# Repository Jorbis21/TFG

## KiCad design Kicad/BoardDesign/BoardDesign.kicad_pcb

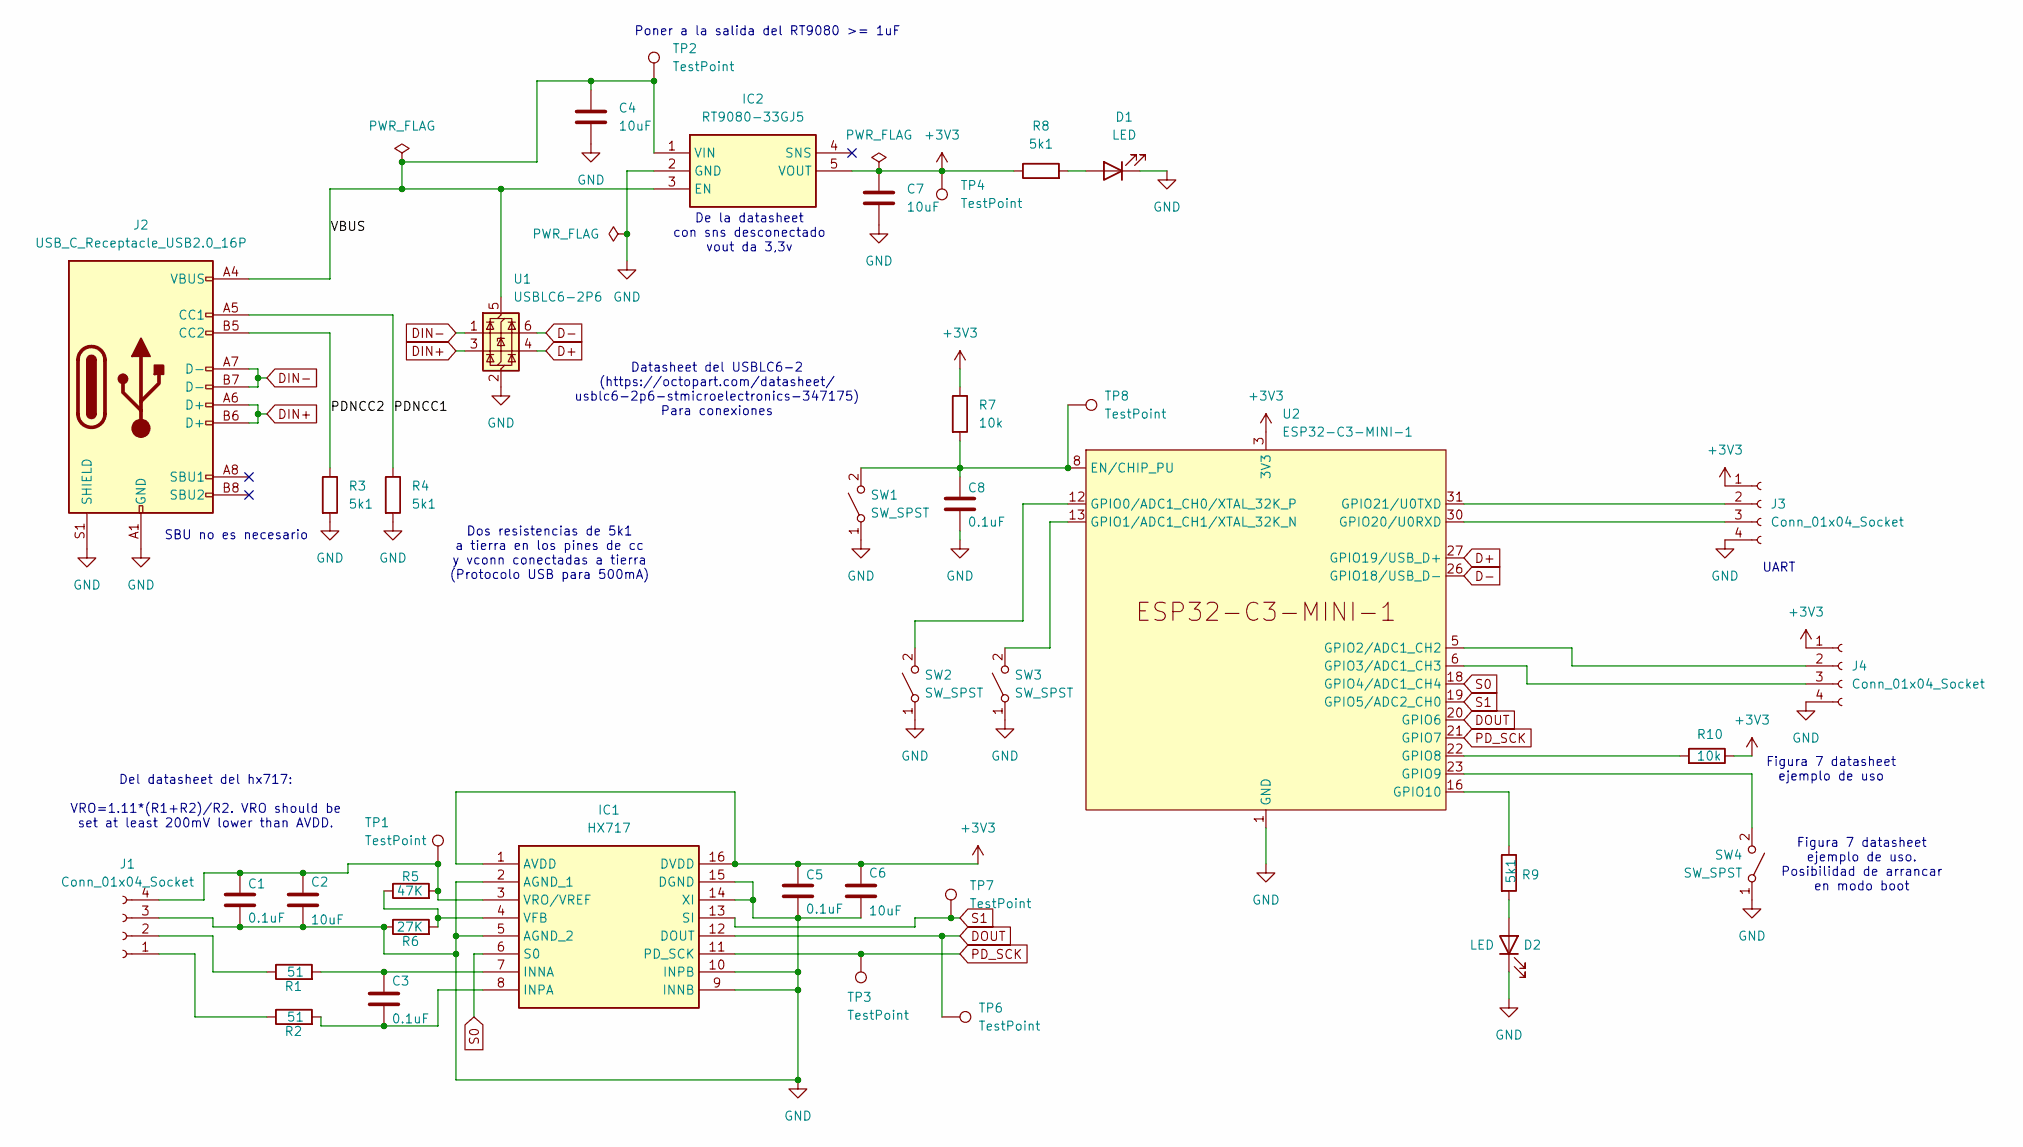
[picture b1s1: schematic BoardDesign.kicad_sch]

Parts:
C1, C3, C5, C8: 0.1uF; C_0603_1608Metric; JLCPCB C14663
C2, C4, C6, C7: 10uF; C_0603_1608Metric; JLCPCB C19702
D1, D2: LED; LED_0603_1608Metric
IC1: HX717; SOP-16_3.9x9.9mm_P1.27mm; Manufacturer_Part_Number HX717; JLCPCB C575394
IC2: RT9080-33GJ5; TSOT-23-5; Manufacturer_Part_Number RT9080-33GJ5; Mouser Part Number 835-RT9080-33GJ5
J1, J3, J4: Conn_01x04_Socket; PinHeader_1x04_P2.54mm_Vertical; JLCPCB C5116483
J2: USB_C_Receptacle_USB2.0_16P; USB_C_Receptacle_GCT_USB4105-xx-A_16P_TopMnt_Horizontal; JLCPCB C5116483
R1, R2: 51; R_0603_1608Metric
R3, R4, R8, R9: 5k1; R_0603_1608Metric
R5: 47K; R_0603_1608Metric
R6: 27K; R_0603_1608Metric
R7, R10: 10k; R_0603_1608Metric
SW1, SW2, SW3, SW4: SW_SPST; TS1187ABAB; JLCPCB C318884
TP1, TP2, TP3, TP4, TP6, TP7, TP8: TestPoint; TestPoint_Pad_D1.5mm_nosilk
U1: USBLC6-2P6; SOT-666; JLCPCB C2827693
U2: ESP32-C3-MINI-1; JLCPCB C2911374

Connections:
+3V3: C5.1, C6.1, C7.1, IC1.1 (AVDD), IC1.16 (DVDD), IC2.5 (VOUT), J3.1, J4.1, R7.1, R8.1, R10.1, TP4.1, U2.3 (3V3)
/PDNCC1: J2.A5 (CC1), R4.1
/PDNCC2: J2.B5 (CC2), R3.1
/VBUS: C4.1, IC2.1 (VIN), IC2.3 (EN), J2.A4 (VBUS), J2.A9 (VBUS), J2.B4 (VBUS), J2.B9 (VBUS), TP2.1, U1.5 (VBUS)
D+: U1.4 (I/O2), U2.27 (GPIO19/USB_D+)
D-: U1.6 (I/O1), U2.26 (GPIO18/USB_D-)
DIN+: J2.A6 (D+), J2.B6 (D+), U1.3 (I/O2)
DIN-: J2.A7 (D-), J2.B7 (D-), U1.1 (I/O1)
DOUT: IC1.12 (DOUT), TP6.1, U2.20 (GPIO6)
GND: C1.2, C2.2, C4.2, C5.2, C6.2, C7.2, C8.2, D1.1 (K), D2.1 (K), IC1.2 (AGND_1), IC1.5 (AGND_2), IC1.9 (INNB), IC1.10 (INPB), IC1.14 (XI), IC1.15 (DGND), IC2.2 (GND), J1.3, J2.A1 (GND), J2.A12 (GND), J2.B1 (GND), J2.B12 (GND), J2.S1 (SHIELD), J3.4, J4.4, R3.2, R4.2, R6.1, SW1.1 (A), SW2.1 (A), SW3.1 (A), SW4.1 (A), U1.2 (GND), U2.1 (GND), U2.2 (GND), U2.11 (GND), U2.14 (GND), U2.36 (GND), U2.37 (GND), U2.38 (GND), U2.39 (GND), U2.40 (GND), U2.41 (GND), U2.42 (GND), U2.43 (GND), U2.44 (GND), U2.45 (GND), U2.46 (GND), U2.47 (GND), U2.48 (GND), U2.49 (GND), U2.50 (GND), U2.51 (GND), U2.52 (GND), U2.53 (GND)
unnamed: D1.2 (A), R8.2
unnamed: D2.2 (A), R9.2
unnamed: C3.1, IC1.7 (INNA), R1.2
unnamed: C3.2, IC1.8 (INPA), R2.2
unnamed: IC1.4 (VFB), R5.1, R6.2
unnamed: C1.1, C2.1, IC1.3 (VRO/VREF), J1.4, R5.2, TP1.1
unnamed: J1.1, R2.1
unnamed: J1.2, R1.1
unnamed: J3.2, U2.31 (GPIO21/U0TXD)
unnamed: J3.3, U2.30 (GPIO20/U0RXD)
unnamed: J4.2, U2.5 (GPIO2/ADC1_CH2)
unnamed: J4.3, U2.6 (GPIO3/ADC1_CH3)
unnamed: C8.1, R7.2, SW1.2 (B), TP8.1, U2.8 (EN/CHIP_PU)
unnamed: SW2.2 (B), U2.12 (GPIO0/ADC1_CH0/XTAL_32K_P)
unnamed: SW3.2 (B), U2.13 (GPIO1/ADC1_CH1/XTAL_32K_N)
unnamed: SW4.2 (B), U2.23 (GPIO9)
unnamed: R10.2, U2.22 (GPIO8)
unnamed: R9.1, U2.16 (GPIO10)
PD_SCK: IC1.11 (PD_SCK), TP3.1, U2.21 (GPIO7)
S0: IC1.6 (S0), U2.18 (GPIO4/ADC1_CH4)
S1: IC1.13 (SI), TP7.1, U2.19 (GPIO5/ADC2_CH0)

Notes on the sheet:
Datasheet del USBLC6-2 (https://octopart.com/datasheet/ usblc6-2p6-stmicroelectronics-347175) Para conexiones
De la datasheet con sns desconectado vout da 3,3v
Del datasheet del hx717: VRO=1.11*(R1+R2)/R2. VRO should be set at least 200mV lower than AVDD.
UART
Poner a la salida del RT9080 >= 1uF
Dos resistencias de 5k1 a tierra en los pines de cc y vconn conectadas a tierra (Protocolo USB para 500mA)
Figura 7 datasheet ejemplo de uso. Posibilidad de arrancar en modo boot
Figura 7 datasheet ejemplo de uso
SBU no es necesario

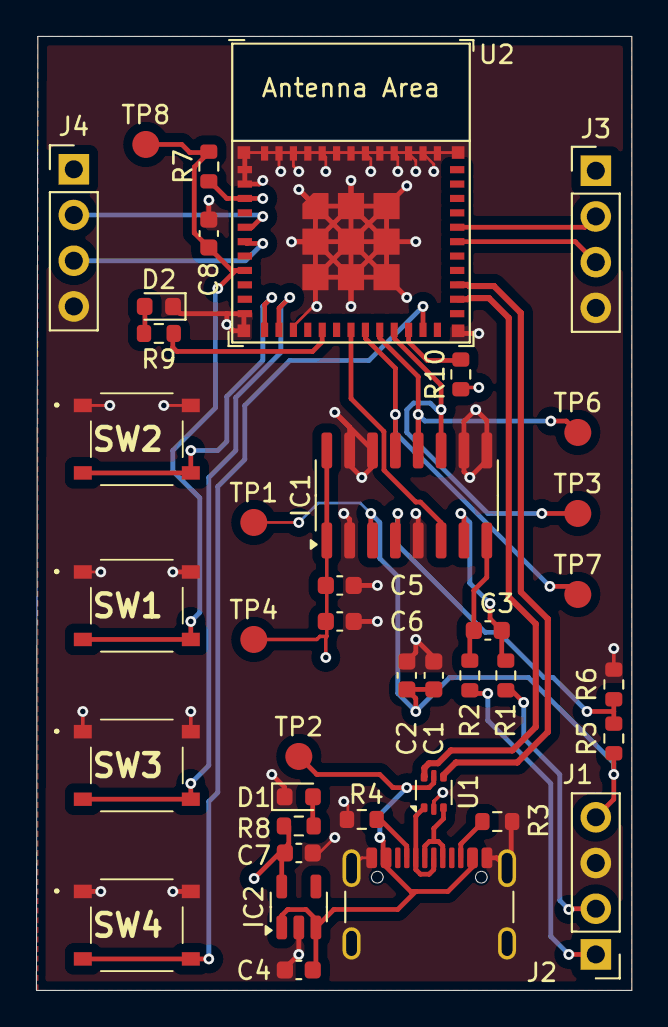
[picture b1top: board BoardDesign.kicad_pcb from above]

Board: 4 copper layers, 33.1 x 53.0 mm, 39 parts (0 on the bottom side), 31 nets.

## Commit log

2024-08-19 Commit inicial
2024-08-19 Documentacion
2024-08-19 CodigoPlaca
2024-08-19 Inicio del codigo de la placa
2024-08-19 float
2024-08-19 todo se envia por BLE
2024-08-19 Recepcion de 's' y 't'
2024-08-19 Falta sincro y tiempo
2024-08-19 Objetivos placa
2024-08-19 kicad
2024-08-19 Codigo casi terminado
2024-08-19 pruebas
2024-08-19 arduino finalizado
2024-08-19 Lista
2024-08-19 Primer commit
    Añadidos componentes básicos (excepto adc) y referencias a JLCPCB
2024-08-19 Todos los componentes
    Falta conectar el hx717 y comprobar valores de resistencias, condensadores, etc.
2024-08-19 Cambios con Dani
2024-08-19 "Inicio rutado kicad"
2024-08-19 Prueba flutter y cambios en la memoria
2024-08-19 Cambios
2024-08-19 Kicad corregido
2024-08-19 Diseño físico casi completo
    Falta comprobar las restricciones intrínsecas del propio receptor usb
2024-08-19 Esto biblioteca no se usa finalmente
2024-08-19 Diseño placa semi terminado
    Faltan un par de footprints
2024-08-19 Intento de añadir BLE
    Me da problemas con la versión de android SDK, no se como solucionarlo.
    El código de ejemplo que he pillado de internet es antiguo así que puede ser por eso.
2024-08-19 cambio pines, placa nueva funcional
2024-08-19 flutter ble y uart
2024-08-19 Revert "flutter ble y uart"
    This reverts commit a848b329df6c82ff8b2492ea8b57e4e55d2d7292.
2024-08-19 borrado
2024-08-19 Flutter ble y uart en desarrollo
2024-08-19 Inicio controlador bluetooth
2024-08-19 Se han generado los archivos de linux y macos
2024-08-19 Reestructuración de la aplicacion de Flutter
    He creado un proyecto nuevo en el que he separado un poco la parte gráfica de la lógica, he añadido logo y boton de bluetooth, zona de recepción de datos. Falta implementar la parte lógica del Blueto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
2024-08-19 Bluetooth casi implementado
    Faltan las llamadas al bluetooth desde home, para comprobar que funcionen y posiblemente modificar el botón de bluetooth. Que de todas formas hay que modificarlo para el cambio de icono según el esta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
2024-08-19 Bluetooth no furrula
2024-08-19 Aplicación en android compila
2024-08-19 Comunicación uart desde placa a aplicación
2024-08-19 Botones añadidos y funcionales
    Solo faltaría poner bonito la recepción de datos, incluyendo lo de tara y sincro realizada.
2024-08-19 Inicio decodificación mensajes
2024-08-19 Falta poner el texto algo más bonito
2024-08-19 Texto inicial quitado
2024-08-20 Cambios en la sincronización
2024-08-29 Docu del esp nuestro en específico
